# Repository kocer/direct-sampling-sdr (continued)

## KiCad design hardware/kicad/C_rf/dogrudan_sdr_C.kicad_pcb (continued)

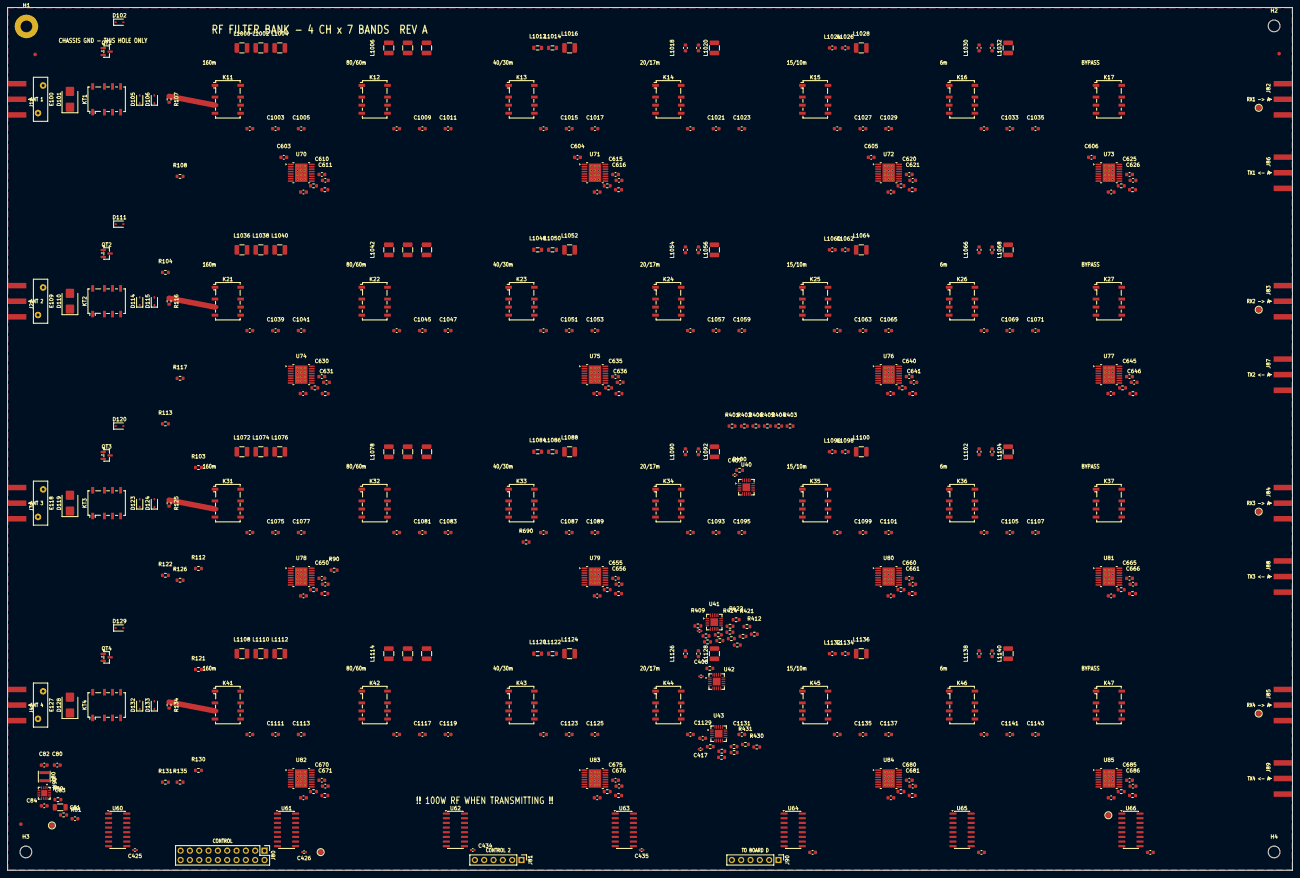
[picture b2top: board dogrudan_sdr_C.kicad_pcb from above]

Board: 2 copper layers, 350.0 x 235.0 mm, 406 parts (0 on the bottom side), 392 nets.

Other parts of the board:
FID1, FID2, FID3: ​FID; Fiducial_1mm_Mask2mm
H1: MountingHole_3.2mm_M3_Pad
H2, H3, H4: MountingHole_3.2mm_M3
TP1: ​+5V; TestPoint_Pad_D1.5mm
TP2: ​+3V3; TestPoint_Pad_D1.5mm
TP3: ​VIN_PROT; TestPoint_Pad_D1.5mm
TP4: ​RX1_OUT; TestPoint_Pad_D1.5mm
TP5: ​RX2_OUT; TestPoint_Pad_D1.5mm
TP6: ​RX3_OUT; TestPoint_Pad_D1.5mm
TP7: ​RX4_OUT; TestPoint_Pad_D1.5mm

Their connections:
+3V3: TP2.1; also elsewhere on the board
RX1_OUT: TP4.1; also elsewhere on the board
RX2_OUT: TP5.1; also elsewhere on the board
RX3_OUT: TP6.1; also elsewhere on the board
RX4_OUT: TP7.1; also elsewhere on the board

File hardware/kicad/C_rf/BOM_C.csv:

Comment,Designator,Footprint,LCSC
0R,"R107,R108,R116,R117,R125,R126,R134,R135,R607,R608,R612,R613,R617,R618,R622,R623,R627,R628,R632,R633,R637,R638,R642,R643,R647,R648,R652,R653,R657,R658,R662,R663,R667,R668,R672,R673,R677,R678,R682,R683,R90",Resistor_SMD:R_0603_1608Metric,C21189
1.5uH,"L1022,L1058,L1094,L1130",Inductor_SMD:L_1210_3225Metric,BASE
100k,"R104,R113,R122,R131",Resistor_SMD:R_0603_1608Metric,C25741
100nF,"C407,C408,C416,C417,C425,C426,C434,C435",Capacitor_SMD:C_0402_1005Metric,C1525
100nF,"C600,C601,C602,C603,C604,C605,C606,C611,C616,C621,C626,C631,C636,C641,C646,C651,C656,C661,C666,C671,C676,C681,C686,C82,C84",Capacitor_SMD:C_0603_1608Metric,C1525
105k,R80,Resistor_SMD:R_0603_1608Metric,C25081
10k,"R400,R401,R402,R403,R404,R405,R406,R409,R410,R411,R412,R413,R414,R415,R418,R419,R420,R421,R422,R423,R424,R427,R428,R429,R430,R431,R432,R433,R690",Resistor_SMD:R_0603_1608Metric,C25744
10nF,"C609,C614,C619,C624,C629,C634,C639,C644,C649,C654,C659,C664,C669,C674,C679,C684",Capacitor_SMD:C_0603_1608Metric,BASE
10uF,C83,Capacitor_SMD:C_1206_3216Metric,C15850
1200pF,"C1007,C1009,C1043,C1045,C1079,C1081,C1115,C1117",Capacitor_SMD:C_0603_1608Metric,BASE
12pF,"C1035,C1071,C1107,C1143",Capacitor_SMD:C_0603_1608Metric,BASE
150nH,"L1024,L1026,L1060,L1062,L1096,L1098,L1132,L1134",Inductor_SMD:L_0603_1608Metric,BASE
180pF,"C1017,C1053,C1089,C1125",Capacitor_SMD:C_0603_1608Metric,BASE
18uH,"L1004,L1040,L1076,L1112",Inductor_SMD:L_1210_3225Metric,BASE
1N4148WS,"D102,D105,D106,D111,D114,D115,D120,D123,D124,D129,D132,D133",Diode_SMD:D_SOD-323,C129905
1k,"R103,R112,R121,R130",Resistor_SMD:R_0603_1608Metric,C21190
1uH,"L1000,L1002,L1006,L1008,L1036,L1038,L1042,L1044,L1072,L1074,L1078,L1080,L1108,L1110,L1114,L1116",Inductor_SMD:L_1210_3225Metric,BASE
2.2uF,"C610,C615,C620,C625,C630,C635,C640,C645,C650,C655,C660,C665,C670,C675,C680,C685",Capacitor_SMD:C_0603_1608Metric,BASE
2.2uH,"L1016,L1052,L1088,L1124",Inductor_SMD:L_1210_3225Metric,C1017
2.2uH,L80,Inductor_SMD:L_Taiyo-Yuden_NR-30xx,C1017
20k,R81,Resistor_SMD:R_0603_1608Metric,C25765
220nH,"L1018,L1020,L1054,L1056,L1090,L1092,L1126,L1128",Inductor_SMD:L_0603_1608Metric,BASE
22uF,"C80,C81",Capacitor_SMD:C_0603_1608Metric,C45783
270pF,"C1025,C1027,C1031,C1033,C1061,C1063,C1067,C1069,C1097,C1099,C1103,C1105,C1133,C1135,C1139,C1141",Capacitor_SMD:C_0603_1608Metric,BASE
2N7002,"QT1,QT2,QT3,QT4",Package_TO_SOT_SMD:SOT-23,C8545
3.3uH,"L1010,L1046,L1082,L1118",Inductor_SMD:L_1210_3225Metric,BASE
33nH,"L1030,L1032,L1066,L1068,L1102,L1104,L1138,L1140",Inductor_SMD:L_0603_1608Metric,BASE
390pF,"C1005,C1011,C1041,C1047,C1077,C1083,C1113,C1119",Capacitor_SMD:C_0603_1608Metric,BASE
470nH,"L1012,L1014,L1048,L1050,L1084,L1086,L1120,L1122",Inductor_SMD:L_0805_2012Metric,BASE
470pF,"C1019,C1021,C1055,C1057,C1091,C1093,C1127,C1129",Capacitor_SMD:C_0603_1608Metric,BASE
56pF,"C1029,C1065,C1101,C1137",Capacitor_SMD:C_0603_1608Metric,BASE
6800pF,"C1001,C1003,C1037,C1039,C1073,C1075,C1109,C1111",Capacitor_SMD:C_0603_1608Metric,BASE
680nH,"L1028,L1064,L1100,L1136",Inductor_SMD:L_1210_3225Metric,BASE
680pF,"C1013,C1015,C1049,C1051,C1085,C1087,C1121,C1123",Capacitor_SMD:C_0603_1608Metric,BASE
68pF,"C1023,C1059,C1095,C1131",Capacitor_SMD:C_0603_1608Metric,BASE
74HC595D,"U60,U61,U62,U63,U64,U65,U66",Package_SO:SOIC-16_3.9x9.9mm_P1.27mm,C5947
820nH,"L1034,L1070,L1106,L1142",Inductor_SMD:L_1210_3225Metric,BASE
A kartina,J80,Connector_PinHeader_2.54mm:PinHeader_2x10_P2.54mm_Vertical,EL
A kartina #2,J81,Connector_PinHeader_2.54mm:PinHeader_1x06_P2.54mm_Vertical,EL
D kartina,J90,Connector_PinHeader_2.54mm:PinHeader_1x06_P2.54mm_Vertical,EL
DRV8833PWPR,"U70,U71,U72,U73,U74,U75,U76,U77,U78,U79,U80,U81,U82,U83,U84,U85",Package_SO:HTSSOP-16-1EP_4.4x5mm_P0.65mm_EP3.4x5mm_Mask2.46x2.31mm_ThermalVias,C53055901
G6K-2F-Y,"KT1,KT2,KT3,KT4",Relay_SMD:Relay_DPDT_Omron_G6K-2F-Y,C80087
G6KU-2F-Y,"K11,K12,K13,K14,K15,K16,K17,K21,K22,K23,K24,K25,K26,K27,K31,K32,K33,K34,K35,K36,K37,K41,K42,K43,K44,K45,K46,K47",Relay_SMD:Relay_DPDT_Omron_G6K-2F-Y,C2153173
GDT 90V,"E100,E109,E118,E127",dogrudan-sdr:GDT_Disc_D12mm_W3.9mm_P7.5mm,C2909520
PE4312C-Z,"U40,U41,U42,U43",Package_DFN_QFN:TQFN-20-1EP_4x4mm_P0.5mm_EP2.1x2.1mm,C500480
RX1 -> A,J82,Connector_Coaxial:SMA_Amphenol_132289_EdgeMount,C496550
RX2 -> A,J83,Connector_Coaxial:SMA_Amphenol_132289_EdgeMount,C496550
RX3 -> A,J84,Connector_Coaxial:SMA_Amphenol_132289_EdgeMount,C496550
RX4 -> A,J85,Connector_Coaxial:SMA_Amphenol_132289_EdgeMount,C496550
SMA anten 1,J1,Connector_Coaxial:SMA_Amphenol_132289_EdgeMount,C496550
SMA anten 2,J2,Connector_Coaxial:SMA_Amphenol_132289_EdgeMount,C496550
SMA anten 3,J3,Connector_Coaxial:SMA_Amphenol_132289_EdgeMount,C496550
SMA anten 4,J4,Connector_Coaxial:SMA_Amphenol_132289_EdgeMount,C496550
SMBJ20A,"D101,D110,D119,D128",Diode_SMD:D_SMB,C364296
TPS62130,U90,Package_DFN_QFN:VQFN-16-1EP_3x3mm_P0.5mm_EP1.68x1.68mm,C337502
TX1 <- A,J86,Connector_Coaxial:SMA_Amphenol_132289_EdgeMount,C496550
TX2 <- A,J87,Connector_Coaxial:SMA_Amphenol_132289_EdgeMount,C496550
TX3 <- A,J88,Connector_Coaxial:SMA_Amphenol_132289_EdgeMount,C496550
TX4 <- A,J89,Connector_Coaxial:SMA_Amphenol_132289_EdgeMount,C496550

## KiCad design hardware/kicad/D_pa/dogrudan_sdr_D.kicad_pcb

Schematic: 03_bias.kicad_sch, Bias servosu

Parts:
C300, C301, C441, C442, C443, C444, C460, C461: 100nF; C_0603_1608Metric
C303, C307, C311, C315: 1uF; C_0603_1608Metric
R302, R305, R306, R309, R310, R313, R314, R317: 10k; R_0603_1608Metric
R304, R308, R312, R316: 100R; R_0603_1608Metric
RS1, RS2, RS3, RS4: 0.01R 2W; R_2512_6332Metric
U20, U21: MCP4922-E/SL; SOIC-14_3.9x8.7mm_P1.27mm
U31, U32, U33, U34: INA240A1DR; SOIC-8_3.9x4.9mm_P1.27mm
U41, U42: LM358; SOIC-8_3.9x4.9mm_P1.27mm

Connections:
ATT_CLK: U20.4 (SCK), U21.4 (SCK); also elsewhere on the board
ATT_DATA: U20.5 (SDI), U21.5 (SDI); also elsewhere on the board
BIAS_CS1: U20.3 (~CS); also elsewhere on the board
BIAS_CS2: U21.3 (~CS); also elsewhere on the board
GATE1: R304.2, R305.1; also elsewhere on the board
GATE2: R308.2, R309.1; also elsewhere on the board
GATE3: R312.2, R313.1; also elsewhere on the board
GATE4: R316.2, R317.1; also elsewhere on the board
IFB1: C303.1, R302.2, U41.2 (-)
IFB2: C307.1, R306.2, U41.6 (-)
IFB3: C311.1, R310.2, U42.2 (-)
IFB4: C315.1, R314.2, U42.6 (-)
IMEAS1: R302.1, U31.5 (OUT); also elsewhere on the board
IMEAS2: R306.1, U32.5 (OUT); also elsewhere on the board
IMEAS3: R310.1, U33.5 (OUT); also elsewhere on the board
IMEAS4: R314.1, U34.5 (OUT); also elsewhere on the board
SRC1: RS1.1, U31.8 (IN+); also elsewhere on the board
SRC2: RS2.1, U32.8 (IN+); also elsewhere on the board
SRC3: RS3.1, U33.8 (IN+); also elsewhere on the board
SRC4: RS4.1, U34.8 (IN+); also elsewhere on the board
VG1: C303.2, R304.1, U41.1
VG2: C307.2, R308.1, U41.7
VG3: C311.2, R312.1, U42.1
VG4: C315.2, R316.1, U42.7
VSET1: U20.14 (VA), U41.3 (+)
VSET2: U20.10 (VB), U41.5 (+)
VSET3: U21.14 (VA), U42.3 (+)
VSET4: U21.10 (VB), U42.5 (+)

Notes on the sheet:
BIAS SERVOSU — tasarimin kalbi
SERVO — CIHAZ BASINA BIR TANE
U42 besleme ayirma
U41 besleme ayirma
'AYARLI A SINIFI' demek, bias'in guc kademesiyle BIRLIKTE degismesi demek. A sinifinda DC cekisi sabittir, cikis gucune bakmaz: bias'i 100 W icin kurup 5 W verirsen yine 333 W yakarsin. ayar Idq @50 V DC isi 5 W 0.33 A 17 W 12 W 10 W 0.67 A 33 W 23 W 25 W 1.67 A 83 W 58 W 50 W 3.33 A 167 W 117 W 75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
KURULUM DAC'i — ORTAK SERI YOLDAN
Iki cift DAC = dort kanal, cihaz basina bir kurulum gerilimi. 12 bit, referans +3V3 -> adim 0.8 mV. Idq 0.33-6.67 A araliginda olcu direncinin cikisina cevrildiginde cozunurluk fazlasiyla yeter.
OLCU DIRENCI 0.01R kaynak bacaginda. 6.67 A / 4 cihaz = 1.67 A cihaz basina -> 16.7 mV dusum, INA240 x20 kazancla 334 mV. Direncte harcanan 28 mW; 2512 govde rahat. INTEGRATOR: hata sifirlanana kadar gecidi surer. RC = 10k x 1uF = 10 ms, bias donguSU RF'ten cok yavas — modulasyonu takip etmez, sade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

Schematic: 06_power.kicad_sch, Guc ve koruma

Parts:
C600, C609, C617, C651, C660, C665, C667, C690: 100nF; C_0603_1608Metric
C601, C602: 470uF; CP_Radial_D16.0mm_P7.50mm
C650: 10uF; C_1206_3216Metric
C661: 22nF; C_0805_2012Metric
C662: 100nF; C_0805_2012Metric
C663: 2.2uF; C_1210_3225Metric
C664: 22uF; C_1206_3216Metric
C666: 22uF; C_0603_1608Metric
D31: SMBJ54A; D_SMB
D607, D610, D611, D612, D613, D614, D615, D616: 1N4148WS; D_SOD-323
J30: 50V giris; TerminalBlock_CUI_TB007-508-02_1x02_P5.08mm_Horizontal
J31: A kartina; PinHeader_2x10_P2.54mm_Vertical
J32: C kartindan; PinHeader_1x06_P2.54mm_Vertical
J33: sonraki PA; PinHeader_2x10_P2.54mm_Vertical
L50: 47uH; L_Taiyo-Yuden_NR-30xx
L51: 2.2uH; L_Taiyo-Yuden_NR-30xx
Q30: IRFB4110PBF; TO-220-3_Vertical
Q31, Q32: 2N7002; SOT-23
QL1, QL2, QL3, QL4, QL5, QL6, QL7: 2N7002; SOT-23
R601, R606, R608: 100k; R_0603_1608Metric
R602: 140k; R_0603_1608Metric
R603: 10k; R_0603_1608Metric
R604: 105k; R_0603_1608Metric
R605: 20k; R_0603_1608Metric
R690: 0R; R_0603_1608Metric
U50: LM5164DDAR; SOIC-8-1EP_3.9x4.9mm_P1.27mm_EP2.29x3mm_ThermalVias
U51: TPS62130; VQFN-16-1EP_3x3mm_P0.5mm_EP1.68x1.68mm
U52: LM74700QDBVRQ1; SOT-23-6
U55: MCP9700AT; SOT-23
U56: 74HC595D; SOIC-16_3.9x9.9mm_P1.27mm
U57: MCP3208T-CI/SL; SOIC-16_3.9x9.9mm_P1.27mm

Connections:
ADC_SDIO: J31.17, J33.7, U57.12 (Dout)
ATT_CLK: J31.5, J33.5, U57.13 (CLK); also elsewhere on the board
ATT_DATA: J31.3, J33.3, U57.11 (Din); also elsewhere on the board
BIAS_CS1: J31.9; also elsewhere on the board
BIAS_CS2: J31.11; also elsewhere on the board
BST_12V: C600.1, U50.7 (BST)
DPD_EN: Q32.1 (G), R606.1
DPD_EN_LO: D607.1 (K), Q32.2 (D); also elsewhere on the board
DRV_EN_LO: Q31.2 (D); also elsewhere on the board
FB_5V: R604.2, R605.1, U51.5 (FB)
FB_12V: R602.2, R603.1, U50.5 (FB)
FLANGE_T: U55.2 (V_{OUT}), U57.1 (CH0)
FWD_LOG: U57.2 (CH1); also elsewhere on the board
GND_HDR: J31.2, J31.4, J31.6, J31.8, J31.10, J31.12, J31.14, J31.16, J31.18, J31.19, J31.20, R690.1
IMEAS1: U57.4 (CH3); also elsewhere on the board
IMEAS2: U57.5 (CH4); also elsewhere on the board
IMEAS3: U57.6 (CH5); also elsewhere on the board
IMEAS4: U57.7 (CH6); also elsewhere on the board
KL1_LO: D610.1 (K), QL1.2 (D); also elsewhere on the board
KL2_LO: D611.1 (K), QL2.2 (D); also elsewhere on the board
KL3_LO: D612.1 (K), QL3.2 (D); also elsewhere on the board
KL4_LO: D613.1 (K), QL4.2 (D); also elsewhere on the board
KL5_LO: D614.1 (K), QL5.2 (D); also elsewhere on the board
KL6_LO: D615.1 (K), QL6.2 (D); also elsewhere on the board
KL7_LO: D616.1 (K), QL7.2 (D); also elsewhere on the board
LQ0: QL1.1 (G), U56.15 (QA)
LQ1: QL2.1 (G), U56.1 (QB)
LQ2: QL3.1 (G), U56.2 (QC)
LQ3: QL4.1 (G), U56.3 (QD)
LQ4: QL5.1 (G), U56.4 (QE)
LQ5: QL6.1 (G), U56.5 (QF)
LQ6: QL7.1 (G), U56.6 (QG)
unnamed: L51.1, U51.1 (SW), U51.2 (SW), U51.3 (SW)
PA_ADC_CS: J31.13, U57.10 (~CS/SHDN)
PA_ATT_LE: J31.7; also elsewhere on the board
PA_INHIBIT: J31.15, J33.15, Q31.1 (G), R608.1
REV_LOG: U57.3 (CH2); also elsewhere on the board
RLY_RCLK: J32.3, J33.13, U56.12 (RCLK)
RLY_SER_NEXT: J33.9, U56.9 (QH')
RLY_SER_OUT: J32.1, U56.14 (SER)
RLY_SRCLK: J32.2, J33.11, U56.11 (SRCLK)
RON_12V: R601.1, U50.4 (RON)
SW_12V: C600.2, L50.1, U50.8 (SW)
VCAP50: C660.1, U52.1 (VCAP)
VIN50_G: Q30.1 (G), U52.5 (GATE)

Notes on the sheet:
Yedi LPF rolesi kilitlenmeyen G2RL-2, 12 V bobin. Kilitlenen DEGIL: guc kesilince bypass'a donmeli, filtre yanlis bantta kalmamali. Bobin akimi ~30 mA, 2N7002 rahat. Sonumleme diyodu SART: bobin kesilince endüktif vurus MOSFET'i deler. 74HC595 cikislari MOSFET geçidini suruyor, akimi MOSFET veriyor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
** A KARTINDA YER YOK. ** Banka 0 ve 1 dolu (bkz 08_control). PA'nin istedigi 12 hat icin uc secenek: 1 C kartindaki kaydirmali yazmac zincirini uzat — PA'nin ayar hatlari zaten yavas, seri gitmesinde sakinca yok 2 FLANGE_T, FWD_LOG, REV_LOG icin A kartina kucuk bir ADC (MCP3208 sinifi) ekle, SPI'i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
final 50 V / 6.7 A = 333 W (A sinifi 100 W) surucu 2 12 V / 1.0 A = 12 W lojik+lojik 5 V ve 3.3 V = 5 W -------- toplam ~350 W
SONRAKI PA KARTINA — ZINCIR GECISI
50 V --LM5164--> 12 V --TPS62130--> 5 V Ilk cizimde turev raylar 50 V ve 24 V'tan TPS62130 ile aliniyordu. O parcanin giris tavani 17 V; ikisi de yanlisti ve kart ilk aciliste olurdu. 24 V rayi kalkti, surucu 2 artik 12 V'tan. LM5164: 100 V giris, 1 A, sabit acik-zamanli. RON direnci anahtarlama fr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
TMP235 FLANSTA, cihazlarin dibinde. 10 mV/C, FPGA ADC'siyle okunuyor. 233 W dagitan bir kartta sicaklik olcumu tercih degil. PA_INHIBIT hatti: FPGA sifirlaninca ya da besleme yokken 100k asagi cekiyor, MOSFET kapali, surucu ETKIN DEGIL. Guvenlik varsayilan durumdan gelmeli. KESME SARTLARI (FPGA'da,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
TUREV RAYLAR
KONTROL ARAYUZU — A kartina
TERS POLARITE — IDEAL DIYOT (LM74700-Q1 + IRFB4110) Eski cozum IRF9540N P-MOSFET'ti: 0.117 ohm x 6.67 A^2 = 5.2 W. Sogutucusuz TO-220'de 320 C artis demek, yani parca 100 W'lik ilk veriste olurdu. Simdi 3.7 mohm x 6.67 A^2 = 0.17 W; sogutucu gerekmiyor, kartin ortasinda durabilir. 15 V zener KALKTI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
KORUMA — donanimda, yazilimda degil
YEREL OLCUM ADC'si
LPF ROLE SURUCUSU
DORT PA'YA KADAR BUYUR, A KARTINDA EK PIN ISTEMEDEN. Paylasilan: ATT_DATA, ATT_CLK, ADC_SDIO. Bunlar veri yolu, her kart ayni hatti dinliyor. Karta ozel olan secme sinyalleri (ATT_LE, BIAS_CS, ADC_CS) FPGA'dan gelmiyor — her kart kendi 74HC595'inden uretiyor. Zincir A -> C -> D1 -> D2 -> D3 -> D4 d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
GUC VE KORUMA
Sekiz kanaldan yedisi kullaniliyor: flans sicakligi, ileri ve yansiyan guc, ve DORT CIHAZIN DRAIN AKIMI. Akim olcumlerini de buraya baglamak bedavaydi ve degerli: bias servosu kapali cevrim calisiyor ama FPGA'nin gercek akimi GORMESI gerekiyor — servo bozulsa, bir cihaz akimin cogunu cekse ya da te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

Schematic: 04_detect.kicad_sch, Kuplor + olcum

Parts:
C401, C403: 1nF; C_0603_1608Metric
C406, C412: 220pF; C_0603_1608Metric
C407, C408, C409, C413, C414, C415: 100nF; C_0603_1608Metric
J20: DPD -> C karti; SMA_Amphenol_132289_EdgeMount
J40: ANTEN -> panel SO-239; Altech_AK100_1x02_P5.00mm
K20: G6K-2F-Y; Relay_DPDT_Omron_G6K-2F-Y
R160, R161: 500R; R_0603_1608Metric
R400, R402: 51R 1%; R_2512_6332Metric
R404, R410: 19R1; R_0603_1608Metric
R405, R411: 247R; R_0603_1608Metric
R416: 51R; R_0603_1608Metric
T20, T21: FT50-43 1:32; XFMR_Toroid_4P_Vertical
U60, U61: AD8318ACPZ; NXP_VQFN-16-1EP_4x4mm_P0.65mm_EP2.1x2.1mm

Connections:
ANT_OUT: J40.1, T20.2 (AB), T21.3 (SA)
CPL_COM: R400.2, R402.2, T21.1 (AA)
DPD_EN_LO: K20.8 (COIL-); also elsewhere on the board
DPD_OUT: J20.1 (In), K20.4 (NO1)
DPD_TERM: K20.2 (NC1), R416.1
FWD_AC: C401.2, K20.3 (COM1), R404.1, R405.1
FWD_CLPF: C406.1, U60.5 (CLPF)
FWD_DET: R405.2, U60.14 (INHI)
FWD_LOG: U60.6 (VOUT), U60.7 (VSET); also elsewhere on the board
FWD_RAW: C401.1, R400.1, T20.3 (SA)
FWD_TADJ: R160.1, U60.10 (TADJ)
PA_LPF_OUT: T20.1 (AA); also elsewhere on the board
REV_AC: C403.2, R410.1, R411.1
REV_CLPF: C412.1, U61.5 (CLPF)
REV_DET: R411.2, U61.14 (INHI)
REV_LOG: U61.6 (VOUT), U61.7 (VSET); also elsewhere on the board
REV_RAW: C403.1, R402.1, T20.4 (SB)
REV_TADJ: R161.1, U61.10 (TADJ)

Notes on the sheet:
Uc is birden yapiyor: 1 KAPALI CEVRIM GUC KONTROLU — kademeler kalibreli olsun 2 SWR KORUMASI — anten yokken verirsen final olmesin 3 DPD ORNEKLEME — bozulmanin tersini hesaplamak icin PA kazanci sicaklikla, beslemeyle ve bantla degisir. Zayiflaticiyi acik cevrim ayarlamak 'yaklasik 50 W' verir; ol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
ANTEN CIKISI
SO-239 kasaya, karta kisa koaksiyel. 100 W'ta SMA da tasir ama amator istasyonun kablo tarafi PL-259; donusturucu eklemek her baglantida bir kayip ve bir arizali temas noktasi daha demek. Terminal 1.5 sqmm lehim teli icin: 100 W / 50 ohm = 1.4 A, ama SWR 3:1'de tepe akim iki katina cikiyor.
VSET cikisa bagli = OLCUM modu (kontrol modu degil). Cikis girise logaritmik: -25 mV/dB, 0 dBm'de ~0.5 V. Giris araligi -60..0 dBm, yani 60 dB. Tandem kuplor + sont zayiflatici birlikte ~-50 dB: 100 W'ta detektor ~0 dBm goruyor, 100 mW'ta -30 dBm. Butun guc merdiveni araligin icinde. Kesin degeri d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
DETEKTORLER — AD8318 x2
DPD ORNEKLEME YOLU
Kuplorun ileri ornegi bir role uzerinden C kartina, oradan RX4 girisine gidiyor. FPGA cikisi ornekleyip bozulmanin tersini hesapliyor ve gonderilen orneklere onceden uyguluyor. VERIRKEN ZATEN ALAMIYORUZ (TASARIM.md §8.3) — dort RX kanali bosta. Kuplor guc olcumu icin zaten kondu. FPGA orada. EKLENE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
YONLU KUPLOR VE OLCUM
KUPLOR — tandem match, akim + gerilim ornegi
FT50-43 x2. T20: birincil 1 sarim (duz gecen tel), ikincil 32. T21: 32 sarim hat-toprak arasi, 1 sarim CPL_COM'a. Akim ornegi 51 x I/32, gerilim ornegi V/32. Toplam ileri porta, fark yansiyan porta gidiyor; 50 ohm yukte yansiyan port sifir. Bir onceki devrede REV yapisi geregi sifirdi — arasindaki 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

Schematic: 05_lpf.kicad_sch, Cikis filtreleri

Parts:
C500, C508: 1600pF; C_Disc_D7.5mm_W5.0mm_P5.00mm
C502: 360pF; C_Disc_D7.5mm_W5.0mm_P5.00mm
C503: 56pF; C_1206_3216Metric
C504: 2700pF; C_Disc_D7.5mm_W5.0mm_P5.00mm
C506: 180pF; C_Disc_D7.5mm_W5.0mm_P5.00mm
C507, C516: 4.7pF; C_1206_3216Metric
C509, C517: 820pF; C_Disc_D7.5mm_W5.0mm_P5.00mm
C511: 200pF; C_Disc_D7.5mm_W5.0mm_P5.00mm
C512: 15pF; C_1206_3216Metric
C513: 1500pF; C_Disc_D7.5mm_W5.0mm_P5.00mm
C515, C545, C553: 91pF; C_Disc_D7.5mm_W5.0mm_P5.00mm
C518, C526: 560pF; C_Disc_D7.5mm_W5.0mm_P5.00mm
C520: 120pF; C_Disc_D7.5mm_W5.0mm_P5.00mm
C521: 3pF; C_1206_3216Metric
C522: 1000pF; C_Disc_D7.5mm_W5.0mm_P5.00mm
C524, C547: 51pF; C_Disc_D7.5mm_W5.0mm_P5.00mm
C525, C543: 3.6pF; C_1206_3216Metric
C527, C535, C540: 270pF; C_Disc_D7.5mm_W5.0mm_P5.00mm
C529, C536, C544, C549: 160pF; C_Disc_D7.5mm_W5.0mm_P5.00mm
C530: 12pF; C_1206_3216Metric
C531: 430pF; C_Disc_D7.5mm_W5.0mm_P5.00mm
C533: 75pF; C_Disc_D7.5mm_W5.0mm_P5.00mm
C534, C552: 1.6pF; C_1206_3216Metric
C538, C554, C562: 62pF; C_Disc_D7.5mm_W5.0mm_P5.00mm
C539: 6.8pF; C_1206_3216Metric
C542: 27pF; C_Disc_D7.5mm_W5.0mm_P5.00mm
C548: 2.2pF; C_1206_3216Metric
C551: 22pF; C_Disc_D7.5mm_W5.0mm_P5.00mm
C556: 13pF; C_Disc_D7.5mm_W5.0mm_P5.00mm
C557: 1.1pF; C_1206_3216Metric
C558: 110pF; C_Disc_D7.5mm_W5.0mm_P5.00mm
C560: 5.1pF; C_Disc_D7.5mm_W5.0mm_P5.00mm
C561: 1.2pF; C_1206_3216Metric
KL1, KL2, KL3, KL4, KL5, KL6, KL7: G2RL-2 DC12; Relay_DPDT_Omron_G2RL-2
L501, L505: T94-2 24s; L_Toroid_T94_Vertical
L510, L514: T94-2 17s; L_Toroid_T94_Vertical
L519, L523: T94-2 15s; L_Toroid_T94_Vertical
L528, L532: T68-2 12s; L_Toroid_T68_Vertical
L537, L541: T68-2 10s; L_Toroid_T68_Vertical
L546, L550: T50-6 9s; L_Toroid_T50_Vertical
L555, L559: T50-6 7s; L_Toroid_T50_Vertical
R500, R501: 0R; R_0603_1608Metric

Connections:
KL1_LO: KL1.A2 (COIL-); also elsewhere on the board
KL2_LO: KL2.A2 (COIL-); also elsewhere on the board
KL3_LO: KL3.A2 (COIL-); also elsewhere on the board
KL4_LO: KL4.A2 (COIL-); also elsewhere on the board
KL5_LO: KL5.A2 (COIL-); also elsewhere on the board
KL6_LO: KL6.A2 (COIL-); also elsewhere on the board
KL7_LO: KL7.A2 (COIL-); also elsewhere on the board
LF1_A: C500.1, C502.1, C503.1, KL1.14 (NO1), L501.1
LF1_B: C506.2, C507.2, C508.1, KL1.24 (NO2), L505.2
LF2_A: C509.1, C511.1, C512.1, KL2.14 (NO1), L510.1
LF2_B: C515.2, C516.2, C517.1, KL2.24 (NO2), L514.2
LF3_A: C518.1, C520.1, C521.1, KL3.14 (NO1), L519.1
LF3_B: C524.2, C525.2, C526.1, KL3.24 (NO2), L523.2
LF4_A: C527.1, C529.1, C530.1, KL4.14 (NO1), L528.1
LF4_B: C533.2, C534.2, C535.1, KL4.24 (NO2), L532.2
LF5_A: C536.1, C538.1, C539.1, KL5.14 (NO1), L537.1
LF5_B: C542.2, C543.2, C544.1, KL5.24 (NO2), L541.2
LF6_A: C545.1, C547.1, C548.1, KL6.14 (NO1), L546.1
LF6_B: C551.2, C552.2, C553.1, KL6.24 (NO2), L550.2
LF7_A: C554.1, C556.1, C557.1, KL7.14 (NO1), L555.1
LF7_B: C560.2, C561.2, C562.1, KL7.24 (NO2), L559.2
LPF_B1_IN: KL1.11 (COM1), R500.2
LPF_B1_OUT: KL1.21 (COM2), R501.1
LPF_B2_IN: KL1.12 (NC1), KL2.11 (COM1)
LPF_B2_OUT: KL1.22 (NC2), KL2.21 (COM2)
LPF_B3_IN: KL2.12 (NC1), KL3.11 (COM1)
LPF_B3_OUT: KL2.22 (NC2), KL3.21 (COM2)
LPF_B4_IN: KL3.12 (NC1), KL4.11 (COM1)
LPF_B4_OUT: KL3.22 (NC2), KL4.21 (COM2)
LPF_B5_IN: KL4.12 (NC1), KL5.11 (COM1)
LPF_B5_OUT: KL4.22 (NC2), KL5.21 (COM2)
LPF_B6_IN: KL5.12 (NC1), KL6.11 (COM1)
LPF_B6_OUT: KL5.22 (NC2), KL6.21 (COM2)
LPF_B7_IN: KL6.12 (NC1), KL7.11 (COM1)
LPF_B7_OUT: KL6.22 (NC2), KL7.21 (COM2)
N1_1: C502.2, C503.2, C504.1, C506.1, C507.1, L501.2, L505.1
N2_1: C511.2, C512.2, C513.1, C515.1, C516.1, L510.2, L514.1
N3_1: C520.2, C521.2, C522.1, C524.1, C525.1, L519.2, L523.1
N4_1: C529.2, C530.2, C531.1, C533.1, C534.1, L528.2, L532.1
N5_1: C538.2, C539.2, C540.1, C542.1, C543.1, L537.2, L541.1
N6_1: C547.2, C548.2, C549.1, C551.1, C552.1, L546.2, L550.1
N7_1: C556.2, C557.2, C558.1, C560.1, C561.1, L555.2, L559.1
PA_LPF_OUT: KL7.12 (NC1), KL7.22 (NC2), R501.2; also elsewhere on the board
PA_OUT: R500.1; also elsewhere on the board

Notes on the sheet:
SEBEKE SIRASI: once bant secilir, SONRA veris baslar. Role RF altinda anahtarlanirsa kontak ark yapar ve yapisir. Firmware sirasi: LPF rolesi -> 20 ms bekle -> T/R -> 10 ms -> bias kur -> surucuyu ac. Kapanista tersi.
DEGERLER — 5. derece Chebyshev 0.1 dB, C-L-C-L-C g = 1.1468 / 1.3712 / 1.9750 / 1.3712 / 1.1468 Kesim frekanslari: 2.2 / 6.0 / 11 / 19 / 31 / 56 MHz Bobinler HAVA CEKIRDEKLI ya da T68-2 sinifi toz demir: 100 W'ta ferrit doyar ve harmonik URETIR — tam engellemeye calistigin sey. Kondansatorler mika/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
A sinifi bile harmonik uretir. 100 W'ta ikinci harmonik -30 dBc olsa 100 mW eder — yasal sinirin cok ustunde. 5. derece Chebyshev alcak geciren, bant basina bir tane. Kesim frekansi bandin ustunden %10 yukarida; ikinci harmonikte en az 35 dB bastirma veriyor. ** BU FILTRELER C KARTINDAKINDEN TAMAME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
CIKIS HARMONIK FILTRELERI — 7 pozisyon
Zincir giris/cikisi. 0R yerine dogrudan tel de olurdu ama yerlesimde olcum noktasi olarak ise yariyor.

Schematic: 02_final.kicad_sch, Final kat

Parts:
C202: 100nF; C_1206_3216Metric
C203: 1uF; C_1206_3216Metric
C204: 10uF; C_1206_3216Metric
C206, C208: 1nF; C_1206_3216Metric
C230, C231, C232, C233: 100nF; C_0603_1608Metric
L20: 10uH bogucu; L_Toroid_T50_Vertical
Q10, Q11, Q12, Q13: IRFP250N; TO-247-3_Vertical
R200, R201: 1R; R_2512_6332Metric
R205, R207: 820R; R_2512_6332Metric
R240, R241, R242, R243: 10R; R_0603_1608Metric
R244, R245, R246, R247: 1k; R_0603_1608Metric
T30: BN43-202 3:1; XFMR_Toroid_4P_Vertical
T31: BN43-3312 2:4 CT; XFMR_Toroid_5P_Vertical

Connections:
DRN_A: Q10.2 (D), Q11.2 (D), R205.1, T31.1 (PRI_A)
DRN_B: Q12.2 (D), Q13.2 (D), R207.1, T31.2 (PRI_B)
DRN_CT: C202.1, C203.1, C204.1, L20.2, T31.5 (PRI_CT); also elsewhere on the board
DRV_OUT: T30.1 (AA); also elsewhere on the board
FB_A: C206.1, R205.2
FB_B: C208.1, R207.2
G10: Q10.1 (G), R240.2, R244.2
G11: Q11.1 (G), R241.2, R245.2
G12: Q12.1 (G), R242.2, R246.2
G13: Q13.1 (G), R243.2, R247.2
GATE1: R244.1; also elsewhere on the board
GATE2: R245.1; also elsewhere on the board
GATE3: R246.1; also elsewhere on the board
GATE4: R247.1; also elsewhere on the board
GC10: C230.2, R240.1
GC11: C231.2, R241.1
GC12: C232.2, R242.1
GC13: C233.2, R243.1
GIN_A: C206.2, C230.1, C231.1, R200.1, T30.3 (SA)
GIN_B: C208.2, C232.1, C233.1, R201.1, T30.4 (SB)
PA_OUT: T31.3 (SEC_A); also elsewhere on the board
SRC1: Q10.3 (S); also elsewhere on the board
SRC2: Q11.3 (S); also elsewhere on the board
SRC3: Q12.3 (S); also elsewhere on the board
SRC4: Q13.3 (S); also elsewhere on the board

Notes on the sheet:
CIHAZLAR — kol basina iki, paralel
HER GECIDE AYRI 10R: paralel MOSFET'ler arasinda parazit osilasyon olur; seri direnc Q'yu dusurup sonduruyor. Bunu atlayan her tasarim 100+ MHz'te osilasyon yasar. GATE1..4 03_bias'tan geliyor, her cihaza AYRI servo. SRC1..4 olcu direnclerine gidiyor — akim paylasimi cihaz basina olculuyor.
Drainden gecide RC negatif geri besleme. Kazanc artik CIHAZIN gm'i ile degil GERI BESLEME AGI ile belirleniyor: cihaz kazanci frekansla duserken geri besleme orani sabit kaldigi icin toplam kazanc duz cikiyor. Motorola AN758/EB104 bu sekilde 2-30 MHz duz calisir. 30 MHz'te 14 dB hedefleyip alcak ba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
CIKIS — 1:4 yukselten trafo
Verici 1.8-30 MHz (DAC 80 MSPS -> birinci Nyquist 40 MHz). RF LDMOS'un parasi VHF/UHF kazancina gidiyor; bizim tavanimiz 30 MHz. HF'te dalga boyu 10-100 m, govde parazitikleri onemsiz — siradan anahtarlama MOSFET'i gercekten calisiyor. 4 x IRFP250N = $1.96. 2 x MRF300 = $250-400. 200 kat. DORT ADET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
BASTIRMA DIRENCI 1R: Ciss'in reaktansi 30 MHz'te 1.02 ohm. Ayni mertebede direnc girisi frekanstan bagimsiz kiliyor, surucu sabit yuk goruyor. Harcadigi 88 mW. Gecit salinimi sadece 0.42 V tepe: A sinifinda buyuk bir durgun akimin etrafinda yuksek egimle modulasyon var (gm ~8 S kol basina), kol bas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
GIRIS — 7:1 dusuren trafo + bastirma direnci
SARIMLAR — manyetik_hesap.py T31 cikis: BN43-3312, birincil 2 sarim ORTA UCLU, ikincil 4. R_dd = Vcc^2/(2*Pout) = 12.5 ohm, yuk 50 -> 1:4 empedans. Sarim sayisi iki sarttan buyugu: endüktans (0.9) ve DOYMA (1.4). 2 sarimda B = 34.6 mT, ferrit-43'un 50 mT sinirinin altinda. Birincil akim 2.8 A rms -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
GERI BESLEME — 1.8-30 MHz duz kazancin sirri
FINAL KAT — 4 x IRFP250N, A sinifi push-pull-paralel

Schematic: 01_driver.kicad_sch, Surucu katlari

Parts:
C10, C11, C12, C111: 100nF; C_0603_1608Metric
C110: 10uF; C_1206_3216Metric
J10: A kartindan TX1; SMA_Amphenol_132289_EdgeMount
L10: 1uH bogucu; L_0805_2012Metric
L11: 10uH bogucu; L_0805_2012Metric
Q20, Q21: IRF530N; TO-220-3_Vertical
R10: 56R 1W; R_2512_6332Metric
R99, R100, R101, R102, R103, R104, R105, R107, R109: 10k; R_0603_1608Metric
R106, R108: 10R; R_0603_1608Metric
T10: BN43-202 2:1; XFMR_Toroid_4P_Vertical
T12: BN43-202 2:3 CT; XFMR_Toroid_5P_Vertical
U10: PE4312C-Z; TQFN-20-1EP_4x4mm_P0.5mm_EP2.1x2.1mm
U11: PGA-103+; SOT-89-3

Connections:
ATT_CLK: U10.4 (Clock); also elsewhere on the board
ATT_DATA: R99.1; also elsewhere on the board
ATT_DAT_Q: R99.2, U10.3 (Data)
ATT_OUT: C10.1, U10.14 (RF2)
D1_IN: C10.2, U11.1 (RF_IN)
D1_OUT: C12.1, L10.1, U11.3 (RF_OUT_DC_IN)
D2_BIAS: R107.1, R109.1
D2_DA: Q20.2 (D), T12.1 (PRI_A)
D2_DB: Q21.2 (D), T12.2 (PRI_B)
D2_GA: R106.1, T10.3 (SA)
D2_GA_S: Q20.1 (G), R106.2, R107.2
D2_GB: R108.1, T10.4 (SB)
D2_GB_S: Q21.1 (G), R108.2, R109.2
D2_IN: C12.2, T10.1 (AA)
DRV_EN_LO: R10.1; also elsewhere on the board
DRV_OUT: T12.3 (SEC_A); also elsewhere on the board
PA_ATT_LE: U10.5 (LE); also elsewhere on the board
PA_C0: R100.2, U10.1 (C16)
PA_C1: R101.2, U10.15 (C8)
PA_C2: R102.2, U10.16 (C4)
PA_C3: R103.2, U10.17 (C2)
PA_C4: R104.2, U10.19 (C1)
PA_C5: R105.2, U10.20 (C0.5)
PGA_BIAS: C11.1, L10.2, R10.2
TX_IN: J10.1 (In), U10.2 (RF1)

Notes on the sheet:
** Q20/Q21 SOGUTUCUSUZ CALISMAZ ** 12 W giris - 8 W RF = 4 W isi, cihaz basina 2 W. Sogutucusuz TO-220: Rth(j-a) 62 C/W -> 124 C artis. Kutu ici 55 C ile Tj ~180 C; IRF530N siniri 175 C. Ikisi de finallerin flansina vidalanacak: 20 C/W'lik bir kanatcikla Tj ~99 C'ye iniyor.
SURUCU KATLARI — +0.5 dBm'den +39 dBm'e
PGA-103+ BESLEMESI PA_INHIBIT ILE KESILIYOR. 56R'nin ust ucu +5V'a degil DRV_EN_LO'ya bagli (06_power'daki MOSFET). FPGA kalkmadan, SWR korumasi attiginda ya da flans sicakligi asildiginda surucu beslemesiz kalir ve final surulmez. Kesme donanimda; yazilimin dogru davranmasina guvenmiyoruz. PGA-103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
SURUCU 2 — IRF530N cifti, +18 dB, ~8 W
SURUCU 2 AB SINIFI, A degil. Bu kat 8 W veriyor; A sinifinda 27 W isi ederdi ve hicbir sey kazandirmazdi — doğrusalligi belirleyen FINAL kat. Sabit bias, servo yok. 12 V besleme: 8 W icin 50 V gereksiz, LM5164 ile 50 V'tan uretiliyor (06_power). (Once burada '24 V' yaziyordu; 24 V rayi guc agacinda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
SURUCU 1 — PGA-103+, +22 dB
SEVIYE AYARI — PE4312
AD9767 cikisi +0.5 dBm PE4312 zayiflatici -1.5 .. -15 dB ince seviye ayari PGA-103+ +22 dB IRF530N cifti +18 dB --------- final girisine +39 dBm (8 W) ZAYIFLATICI DAC'IN ONUNDE DEGIL, BURADA. DAC tam olcege yakin calisirsa SFDR'i en iyi; seviyeyi sayisal kismak bit kaybettirir. Analog tarafta kisma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
ACILISTA 31.5 dB — EN COK ZAYIFLATMA. Veri sayfasi s.6: seri modda bile acilis durumunu C0.5-C16 bacaklarindaki seviye belirliyor. Altisi da yukari = 31.5 dB. PA acilista en sagir halinde; firmware kademeyi yazana kadar final surulmuyor. Tersi 0 dB demekti — acilista tam guc.

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
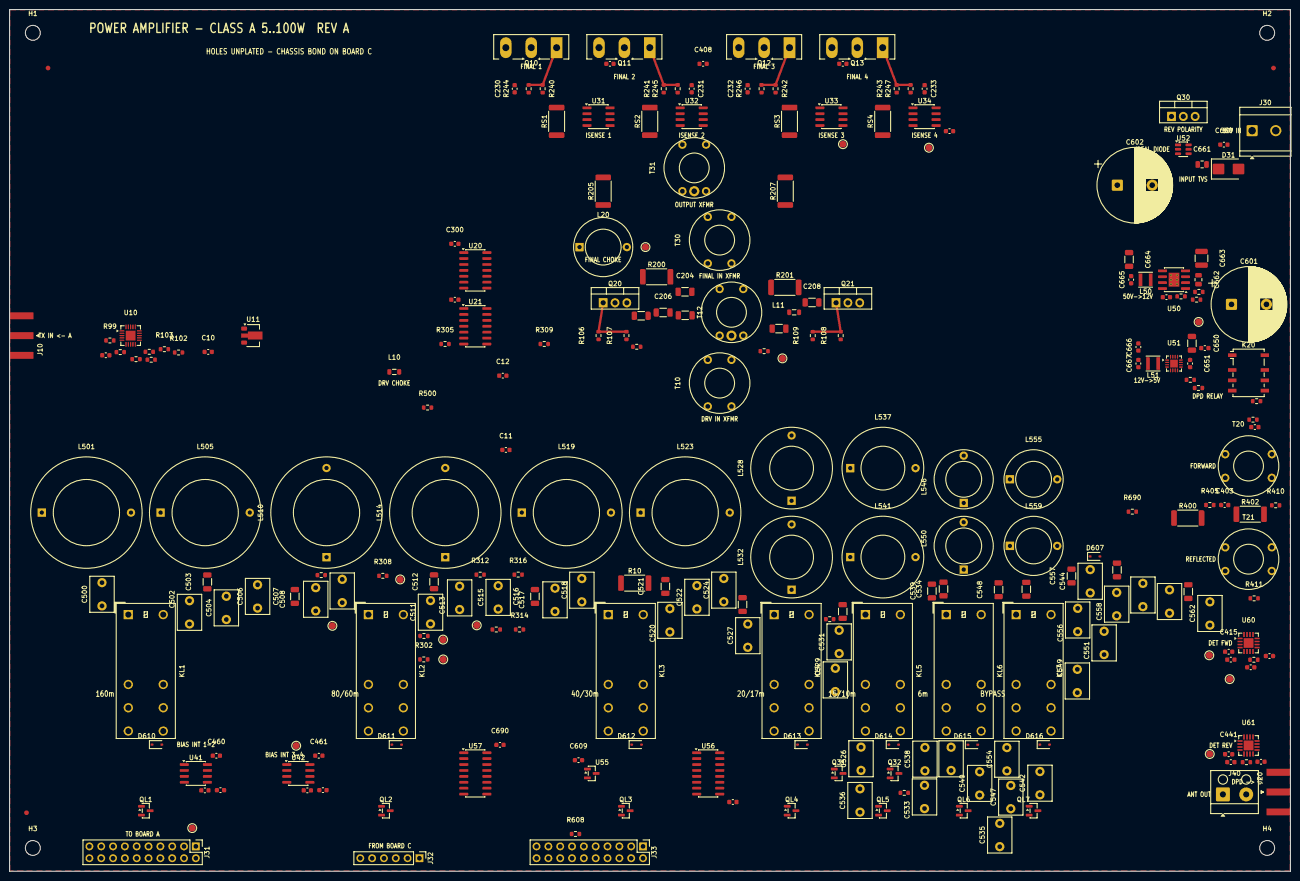
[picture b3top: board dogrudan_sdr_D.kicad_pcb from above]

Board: 2 copper layers, 275.0 x 185.0 mm, 265 parts (0 on the bottom side), 159 nets.

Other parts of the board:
FID1, FID2, FID3: ​FID; Fiducial_1mm_Mask2mm
H1, H2, H3, H4: MountingHole_3.2mm_M3
TP1: ​+50V; TestPoint_Pad_D1.5mm
TP2: ​+12V; TestPoint_Pad_D1.5mm
TP3: ​+5V; TestPoint_Pad_D1.5mm
TP4: ​+3V3; TestPoint_Pad_D1.5mm
TP5: ​DRN_CT; TestPoint_Pad_D1.5mm
TP6: ​GATE1; TestPoint_Pad_D1.5mm
TP7: ​GATE2; TestPoint_Pad_D1.5mm
TP8: ​GATE3; TestPoint_Pad_D1.5mm
TP9: ​GATE4; TestPoint_Pad_D1.5mm
TP10: ​IMEAS1; TestPoint_Pad_D1.5mm
TP11: ​IMEAS2; TestPoint_Pad_D1.5mm
TP12: ​IMEAS3; TestPoint_Pad_D1.5mm
TP13: ​IMEAS4; TestPoint_Pad_D1.5mm
TP14: ​FWD_LOG; TestPoint_Pad_D1.5mm
TP15: ​REV_LOG; TestPoint_Pad_D1.5mm

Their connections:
DRN_CT: TP5.1; also elsewhere on the board
FWD_LOG: TP14.1; also elsewhere on the board
GATE1: TP6.1; also elsewhere on the board
GATE2: TP7.1; also elsewhere on the board
GATE3: TP8.1; also elsewhere on the board
GATE4: TP9.1; also elsewhere on the board
IMEAS1: TP10.1; also elsewhere on the board
IMEAS2: TP11.1; also elsewhere on the board
IMEAS3: TP12.1; also elsewhere on the board
IMEAS4: TP13.1; also elsewhere on the board
REV_LOG: TP15.1; also elsewhere on the board

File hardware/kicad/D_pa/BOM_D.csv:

Comment,Designator,Footprint,LCSC
0.01R 2W,"RS1,RS2,RS3,RS4",Resistor_SMD:R_2512_6332Metric,C2907226
0R,"R500,R501,R690",Resistor_SMD:R_0603_1608Metric,C21189
1.1pF,C557,Capacitor_SMD:C_1206_3216Metric,BASE
1.2pF,C561,Capacitor_SMD:C_1206_3216Metric,BASE
1.6pF,"C534,C552",Capacitor_SMD:C_1206_3216Metric,BASE
1000pF,C522,Capacitor_THT:C_Disc_D7.5mm_W5.0mm_P5.00mm,BASE
100R,"R304,R308,R312,R316",Resistor_SMD:R_0603_1608Metric,C25076
100k,"R601,R606,R608",Resistor_SMD:R_0603_1608Metric,C25741
100nF,"C10,C11,C111,C12,C230,C231,C232,C233,C300,C301,C407,C408,C409,C413,C414,C415,C441,C442,C443,C444,C460,C461,C600,C609,C617,C651,C660,C665,C667,C690",Capacitor_SMD:C_0603_1608Metric,C1525
100nF,C662,Capacitor_SMD:C_0805_2012Metric,C1525
100nF,C202,Capacitor_SMD:C_1206_3216Metric,C1525
105k,R604,Resistor_SMD:R_0603_1608Metric,C25081
10R,"R106,R108,R240,R241,R242,R243",Resistor_SMD:R_0603_1608Metric,C25190
10k,"R100,R101,R102,R103,R104,R105,R107,R109,R302,R305,R306,R309,R310,R313,R314,R317,R603,R99",Resistor_SMD:R_0603_1608Metric,C25744
10uF,"C110,C204,C650",Capacitor_SMD:C_1206_3216Metric,C15850
10uH bogucu,L11,Inductor_SMD:L_0805_2012Metric,C1019
10uH bogucu,L20,dogrudan-sdr:L_Toroid_T50_Vertical,C1019
110pF,C558,Capacitor_THT:C_Disc_D7.5mm_W5.0mm_P5.00mm,BASE
120pF,C520,Capacitor_THT:C_Disc_D7.5mm_W5.0mm_P5.00mm,BASE
12pF,C530,Capacitor_SMD:C_1206_3216Metric,BASE
13pF,C556,Capacitor_THT:C_Disc_D7.5mm_W5.0mm_P5.00mm,BASE
140k,R602,Resistor_SMD:R_0603_1608Metric,C25742
1500pF,C513,Capacitor_THT:C_Disc_D7.5mm_W5.0mm_P5.00mm,BASE
15pF,C512,Capacitor_SMD:C_1206_3216Metric,BASE
1600pF,"C500,C508",Capacitor_THT:C_Disc_D7.5mm_W5.0mm_P5.00mm,BASE
160pF,"C529,C536,C544,C549",Capacitor_THT:C_Disc_D7.5mm_W5.0mm_P5.00mm,BASE
180pF,C506,Capacitor_THT:C_Disc_D7.5mm_W5.0mm_P5.00mm,BASE
19R1,"R404,R410",Resistor_SMD:R_0603_1608Metric,C400656
1N4148WS,"D607,D610,D611,D612,D613,D614,D615,D616",Diode_SMD:D_SOD-323,C129905
1R,"R200,R201",Resistor_SMD:R_2512_6332Metric,C22859
1k,"R244,R245,R246,R247",Resistor_SMD:R_0603_1608Metric,C21190
1nF,"C401,C403",Capacitor_SMD:C_0603_1608Metric,BASE
1nF,"C206,C208",Capacitor_SMD:C_1206_3216Metric,BASE
1uF,"C303,C307,C311,C315",Capacitor_SMD:C_0603_1608Metric,C52923
1uF,C203,Capacitor_SMD:C_1206_3216Metric,C52923
1uH bogucu,L10,Inductor_SMD:L_0805_2012Metric,C1016
2.2pF,C548,Capacitor_SMD:C_1206_3216Metric,BASE
2.2uF,C663,Capacitor_SMD:C_1210_3225Metric,BASE
2.2uH,L51,Inductor_SMD:L_Taiyo-Yuden_NR-30xx,C1017
200pF,C511,Capacitor_THT:C_Disc_D7.5mm_W5.0mm_P5.00mm,BASE
20k,R605,Resistor_SMD:R_0603_1608Metric,C25765
220pF,"C406,C412",Capacitor_SMD:C_0603_1608Metric,BASE
22nF,C661,Capacitor_SMD:C_0805_2012Metric,BASE
22pF,C551,Capacitor_THT:C_Disc_D7.5mm_W5.0mm_P5.00mm,C1554
22uF,C666,Capacitor_SMD:C_0603_1608Metric,C45783
22uF,C664,Capacitor_SMD:C_1206_3216Metric,C45783
247R,"R405,R411",Resistor_SMD:R_0603_1608Metric,C25100
2700pF,C504,Capacitor_THT:C_Disc_D7.5mm_W5.0mm_P5.00mm,BASE
270pF,"C527,C535,C540",Capacitor_THT:C_Disc_D7.5mm_W5.0mm_P5.00mm,BASE
27pF,C542,Capacitor_THT:C_Disc_D7.5mm_W5.0mm_P5.00mm,BASE
2N7002,"Q31,Q32,QL1,QL2,QL3,QL4,QL5,QL6,QL7",Package_TO_SOT_SMD:SOT-23,C8545
3.6pF,"C525,C543",Capacitor_SMD:C_1206_3216Metric,BASE
360pF,C502,Capacitor_THT:C_Disc_D7.5mm_W5.0mm_P5.00mm,BASE
3pF,C521,Capacitor_SMD:C_1206_3216Metric,BASE
4.7pF,"C507,C516",Capacitor_SMD:C_1206_3216Metric,BASE
430pF,C531,Capacitor_THT:C_Disc_D7.5mm_W5.0mm_P5.00mm,BASE
470uF,"C601,C602",Capacitor_THT:CP_Radial_D16.0mm_P7.50mm,BASE
47uH,L50,Inductor_SMD:L_Taiyo-Yuden_NR-30xx,C1020
5.1pF,C560,Capacitor_THT:C_Disc_D7.5mm_W5.0mm_P5.00mm,BASE
500R,"R160,R161",Resistor_SMD:R_0603_1608Metric,BASE
50V giris,J30,TerminalBlock_CUI:TerminalBlock_CUI_TB007-508-02_1x02_P5.08mm_Horizontal,C395880
51R,R416,Resistor_SMD:R_0603_1608Metric,BASE
51R 1%,"R400,R402",Resistor_SMD:R_2512_6332Metric,C22790
51pF,"C524,C547",Capacitor_THT:C_Disc_D7.5mm_W5.0mm_P5.00mm,BASE
560pF,"C518,C526",Capacitor_THT:C_Disc_D7.5mm_W5.0mm_P5.00mm,BASE
56R 1W,R10,Resistor_SMD:R_2512_6332Metric,C22787
56pF,C503,Capacitor_SMD:C_1206_3216Metric,BASE
6.8pF,C539,Capacitor_SMD:C_1206_3216Metric,BASE
62pF,"C538,C554,C562",Capacitor_THT:C_Disc_D7.5mm_W5.0mm_P5.00mm,BASE
74HC595D,U56,Package_SO:SOIC-16_3.9x9.9mm_P1.27mm,C5947
75pF,C533,Capacitor_THT:C_Disc_D7.5mm_W5.0mm_P5.00mm,BASE
820R,"R205,R207",Resistor_SMD:R_2512_6332Metric,C23253
820pF,"C509,C517",Capacitor_THT:C_Disc_D7.5mm_W5.0mm_P5.00mm,BASE
91pF,"C515,C545,C553",Capacitor_THT:C_Disc_D7.5mm_W5.0mm_P5.00mm,BASE
A kartina,J31,Connector_PinHeader_2.54mm:PinHeader_2x10_P2.54mm_Vertical,EL
A kartindan TX1,J10,Connector_Coaxial:SMA_Amphenol_132289_EdgeMount,C496550
AD8318ACPZ,"U60,U61",Package_DFN_QFN:NXP_VQFN-16-1EP_4x4mm_P0.65mm_EP2.1x2.1mm,C578694
ANTEN -> panel SO-239,J40,TerminalBlock_Altech:Altech_AK100_1x02_P5.00mm,EL
BN43-202 2:1,T10,dogrudan-sdr:XFMR_Toroid_4P_Vertical,EL
BN43-202 2:3 CT,T12,dogrudan-sdr:XFMR_Toroid_5P_Vertical,EL
BN43-202 3:1,T30,dogrudan-sdr:XFMR_Toroid_4P_Vertical,EL
BN43-3312 2:4 CT,T31,dogrudan-sdr:XFMR_Toroid_5P_Vertical,EL
C kartindan,J32,Connector_PinHeader_2.54mm:PinHeader_1x06_P2.54mm_Vertical,EL
DPD -> C karti,J20,Connector_Coaxial:SMA_Amphenol_132289_EdgeMount,C496550
FT50-43 1:32,"T20,T21",dogrudan-sdr:XFMR_Toroid_4P_Vertical,EL
G2RL-2 DC12,"KL1,KL2,KL3,KL4,KL5,KL6,KL7",Relay_THT:Relay_DPDT_Omron_G2RL-2,C120133
G6K-2F-Y,K20,Relay_SMD:Relay_DPDT_Omron_G6K-2F-Y,C80087
INA240A1DR,"U31,U32,U33,U34",Package_SO:SOIC-8_3.9x4.9mm_P1.27mm,C2060769
IRF530N,"Q20,Q21",Package_TO_SOT_THT:TO-220-3_Vertical,C2565
IRFB4110PBF,Q30,Package_TO_SOT_THT:TO-220-3_Vertical,C2650
IRFP250N,"Q10,Q11,Q12,Q13",Package_TO_SOT_THT:TO-247-3_Vertical,C2580
LM358,"U41,U42",Package_SO:SOIC-8_3.9x4.9mm_P1.27mm,C7950
LM5164DDAR,U50,Package_SO:SOIC-8-1EP_3.9x4.9mm_P1.27mm_EP2.29x3mm_ThermalVias,C477928
LM74700QDBVRQ1,U52,Package_TO_SOT_SMD:SOT-23-6,C2941042
MCP3208T-CI/SL,U57,Package_SO:SOIC-16_3.9x9.9mm_P1.27mm,C626764
MCP4922-E/SL,"U20,U21",Package_SO:SOIC-14_3.9x8.7mm_P1.27mm,C39851
MCP9700AT,U55,Package_TO_SOT_SMD:SOT-23,C97258
PE4312C-Z,U10,Package_DFN_QFN:TQFN-20-1EP_4x4mm_P0.5mm_EP2.1x2.1mm,C500480
PGA-103+,U11,Package_TO_SOT_SMD:SOT-89-3,C3008207
SMBJ54A,D31,Diode_SMD:D_SMB,C151266
T50-6 7s,"L555,L559",dogrudan-sdr:L_Toroid_T50_Vertical,EL
T50-6 9s,"L546,L550",dogrudan-sdr:L_Toroid_T50_Vertical,EL
T68-2 10s,"L537,L541",dogrudan-sdr:L_Toroid_T68_Vertical,EL
T68-2 12s,"L528,L532",dogrudan-sdr:L_Toroid_T68_Vertical,EL
T94-2 15s,"L519,L523",dogrudan-sdr:L_Toroid_T94_Vertical,EL
T94-2 17s,"L510,L514",dogrudan-sdr:L_Toroid_T94_Vertical,EL
T94-2 24s,"L501,L505",dogrudan-sdr:L_Toroid_T94_Vertical,EL
TPS62130,U51,Package_DFN_QFN:VQFN-16-1EP_3x3mm_P0.5mm_EP1.68x1.68mm,C337502
sonraki PA,J33,Connector_PinHeader_2.54mm:PinHeader_2x10_P2.54mm_Vertical,EL
